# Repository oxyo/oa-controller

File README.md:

## Open Automation Wireless End-Point controller  

This is an Arduino UNO compatible device with 5 relay control channels and Real time clock.
It uses [Ciseco XRF wireless RF radio UART serial data module][] to communicate with Open Automation Center
This is a main controlling element in Open Automation system.  

It can be easily used to control devices like Heaters, Coolers, Fans, Fan Coils, Lights or any other
environment control device in your home.
  
For more information please visit [openautomation.center](http://openautomation.center)

Licensed under [WTFPL license terms](http://www.wtfpl.net/)

[Ciseco XRF wireless RF radio UART serial data module]: http://shop.ciseco.co.uk/xrf-wireless-rf-radio-uart-serial-data-module-xbee-shaped/

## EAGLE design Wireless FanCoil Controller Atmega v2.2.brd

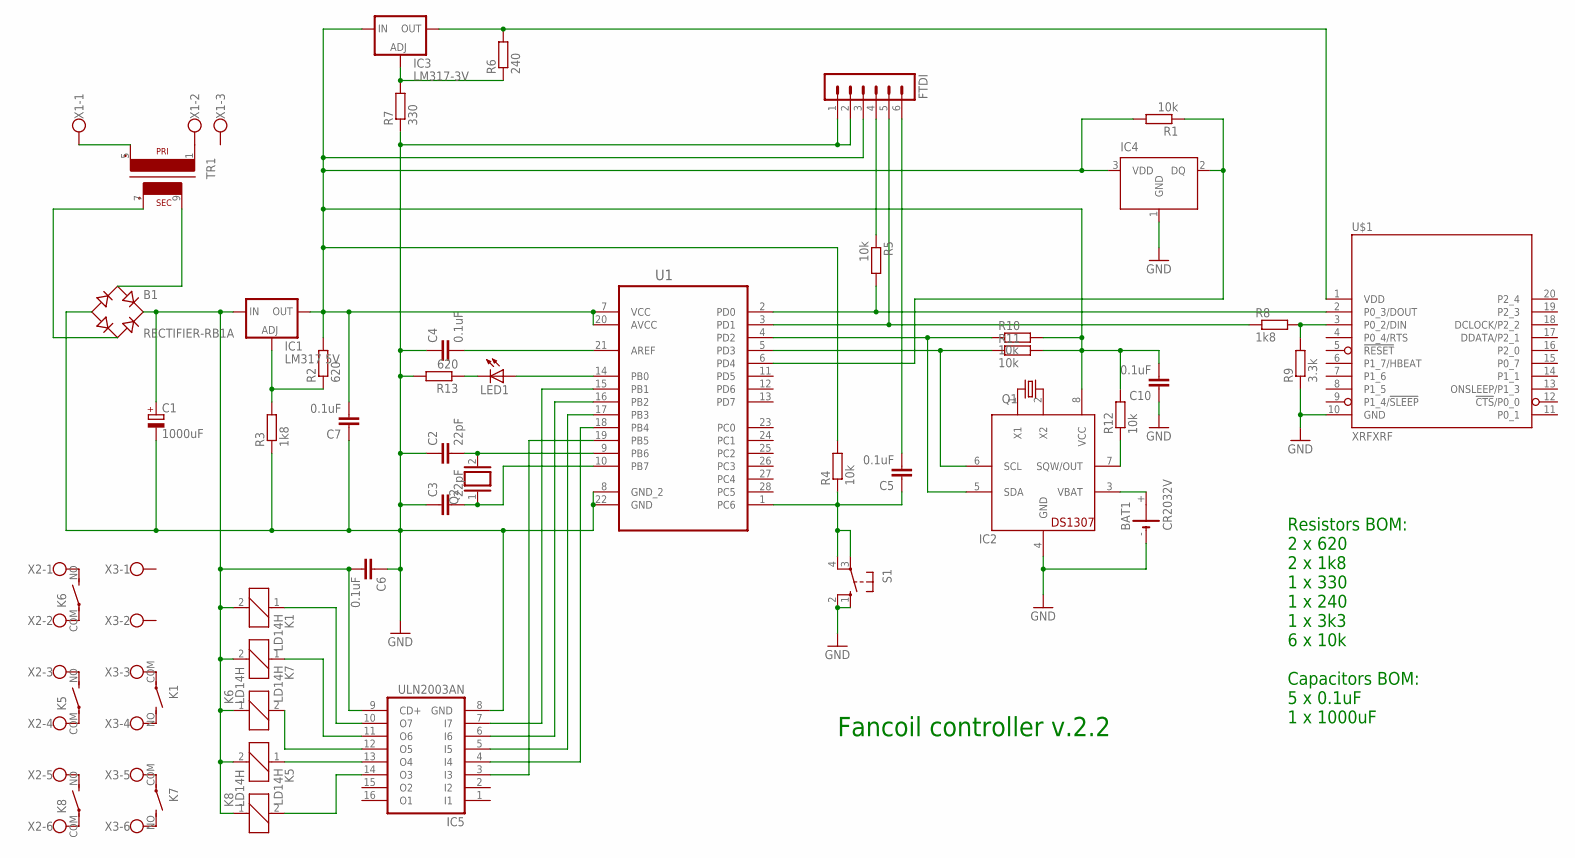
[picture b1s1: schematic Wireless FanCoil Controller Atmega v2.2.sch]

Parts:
B1: RECTIFIER-RB1A; RB1A
BAT1: CR2032V
C1: 1000uF; E5-10,5
C2, C3: 22pF; C025-025X050
C4, C5, C6, C7, C10: 0.1uF; C050-025X075
FTDI: MA06-1
IC1: LM317 5V; 317TS
IC2: DS1307; DIL08
IC3: LM317-3V; 317TS
IC4: DS1820; TO-92
IC5: ULN2003AN; DIL16
K1, K5, K6, K7, K8: LD14H; LD; MPN ALD112
LED1: LED3MM
Q1: CRYSTALTC26H; TC26H
Q2: XTAL/S; QS
R1, R4, R5, R10, R11, R12: 10k; 0207/5V
R2, R13: 620; 0207/5V
R3: 1k8; 0207/5V
R6: 240; 0207/5V
R7: 330; 0207/5V
R8: 1k8; 0207/12
R9: 3.3k; 0207/5V
S1: 10-XX; B3F-10XX
TR1: EI30-1
U1: ATMEGA328P-PU; DIP254P762X457-28
U$1: XRFXRF; XRF
X1: W237-103
X2, X3: W237-136

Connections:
GND: B1.-, BAT1.-, C1.-, C2.1, C3.1, C4.1, C6.1, C7.1, C10.1, FTDI.1, FTDI.2, IC2.4 (GND), IC4.1 (GND), IC5.8 (GND), R3.1, R7.1, R9.1, R13.2, S1.1 (S), S1.2 (S1), U1.8 (GND_2), U1.22 (GND), U$1.10 (GND)
LM317-5V: IC1.1 (ADJ), R2.1, R3.2
unnamed: C4.2, U1.21 (AREF)
unnamed: C5.2, FTDI.6
unnamed: IC2.2 (X2), Q1.1
unnamed: IC2.1 (X1), Q1.2
unnamed: IC5.10 (O7), K1.1
unnamed: IC3.2 (OUT), R6.2, U$1.1 (VDD)
unnamed: C7.2, C10.2, FTDI.3, IC1.2 (OUT), IC2.8 (VCC), IC3.3 (IN), IC4.3 (VDD), R1.2, R2.2, R4.2, R10.2, R11.2, R12.2, U1.7 (VCC), U1.20 (AVCC)
unnamed: TR1.1, X1.2
unnamed: TR1.5 (P2), X1.1
unnamed: B1.+, C1.+, C6.2, IC1.3 (IN), IC5.9 (CD+), K1.2, K5.2, K6.1, K7.2, K8.1
unnamed: B1.AC1, TR1.9 (S4)
unnamed: B1.AC2, TR1.7 (S3)
unnamed: C2.2, Q2.2, U1.9 (PB6)
unnamed: C3.2, Q2.1, U1.10 (PB7)
unnamed: C5.1, R4.1, S1.3, S1.4 (P1), U1.1 (PC6)
unnamed: FTDI.4, R5.1
unnamed: R5.2, U1.2 (PD0), U$1.2 (P0_3/DOUT)
unnamed: FTDI.5, R8.1, U1.3 (PD1)
unnamed: IC3.1 (ADJ), R6.1, R7.2
unnamed: IC2.5 (SDA), R10.1, U1.4 (PD2)
unnamed: R8.2, R9.2, U$1.3 (P0_2/DIN)
unnamed: IC2.6 (SCL), R11.1, U1.5 (PD3)
unnamed: IC2.7 (SQW/OUT), R12.1
unnamed: IC4.2 (DQ), R1.1, U1.6 (PD4)
unnamed: IC5.6 (I6), U1.16 (PB2)
unnamed: K8.NO (S), X2.5
unnamed: IC5.7 (I7), U1.15 (PB1)
unnamed: IC5.4 (I4), U1.18 (PB4)
unnamed: IC5.5 (I5), U1.17 (PB3)
unnamed: IC5.3 (I3), U1.19 (PB5)
unnamed: LED1.K (C), R13.1
unnamed: IC5.14 (O3), K8.2
unnamed: IC5.13 (O4), K5.1
unnamed: IC5.12 (O5), K6.2
unnamed: IC5.11 (O6), K7.1
unnamed: K8.COM, X2.6
unnamed: K5.NO (S), X2.3
unnamed: K5.COM, X2.4
unnamed: K6.NO (S), X2.1
unnamed: K6.COM, X2.2
unnamed: K7.COM, X3.5
unnamed: K7.NO (S), X3.6
unnamed: K1.COM, X3.3
unnamed: LED1.A, U1.14 (PB0)
unnamed: BAT1.+, IC2.3 (VBAT)
unnamed: K1.NO (S), X3.4

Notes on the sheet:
Fancoil controller v.2.2
Resistors BOM: 2 x 620 2 x 1k8 1 x 330 1 x 240 1 x 3k3 6 x 10k Capacitors BOM: 5 x 0.1uF 1 x 1000uF

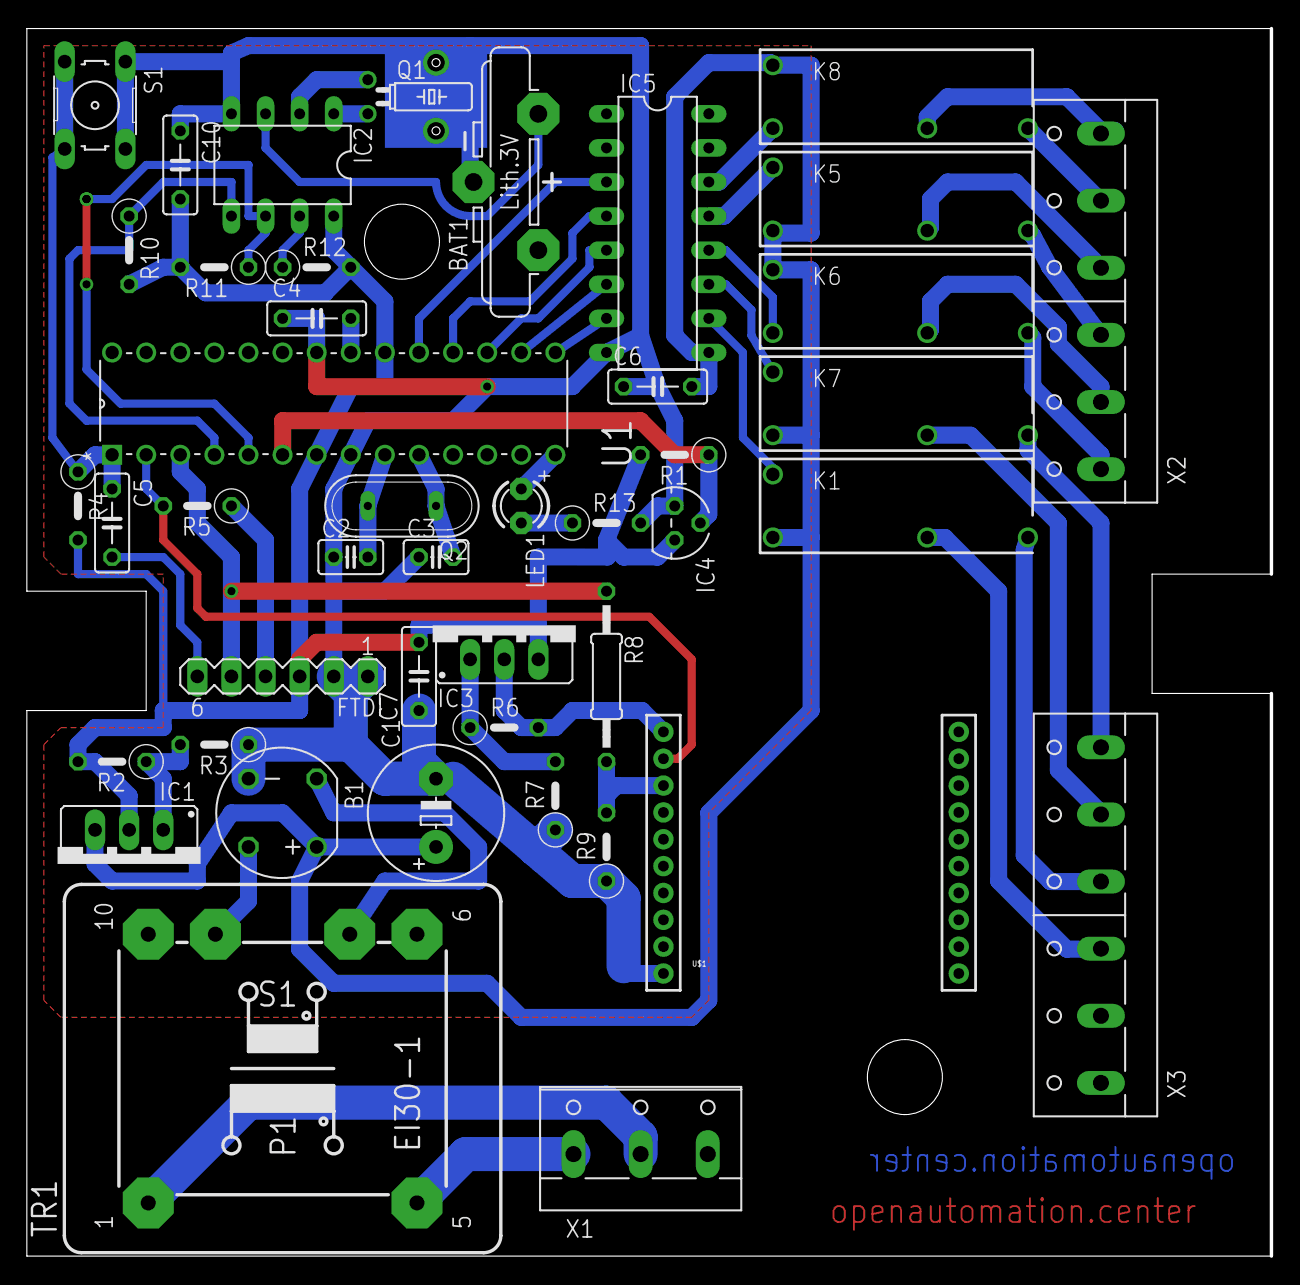
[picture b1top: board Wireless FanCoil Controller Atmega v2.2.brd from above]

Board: 2 copper layers, 92.6 x 91.4 mm, 44 parts (0 on the bottom side), 48 nets.

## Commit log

2015-03-29 Update LICENSE
